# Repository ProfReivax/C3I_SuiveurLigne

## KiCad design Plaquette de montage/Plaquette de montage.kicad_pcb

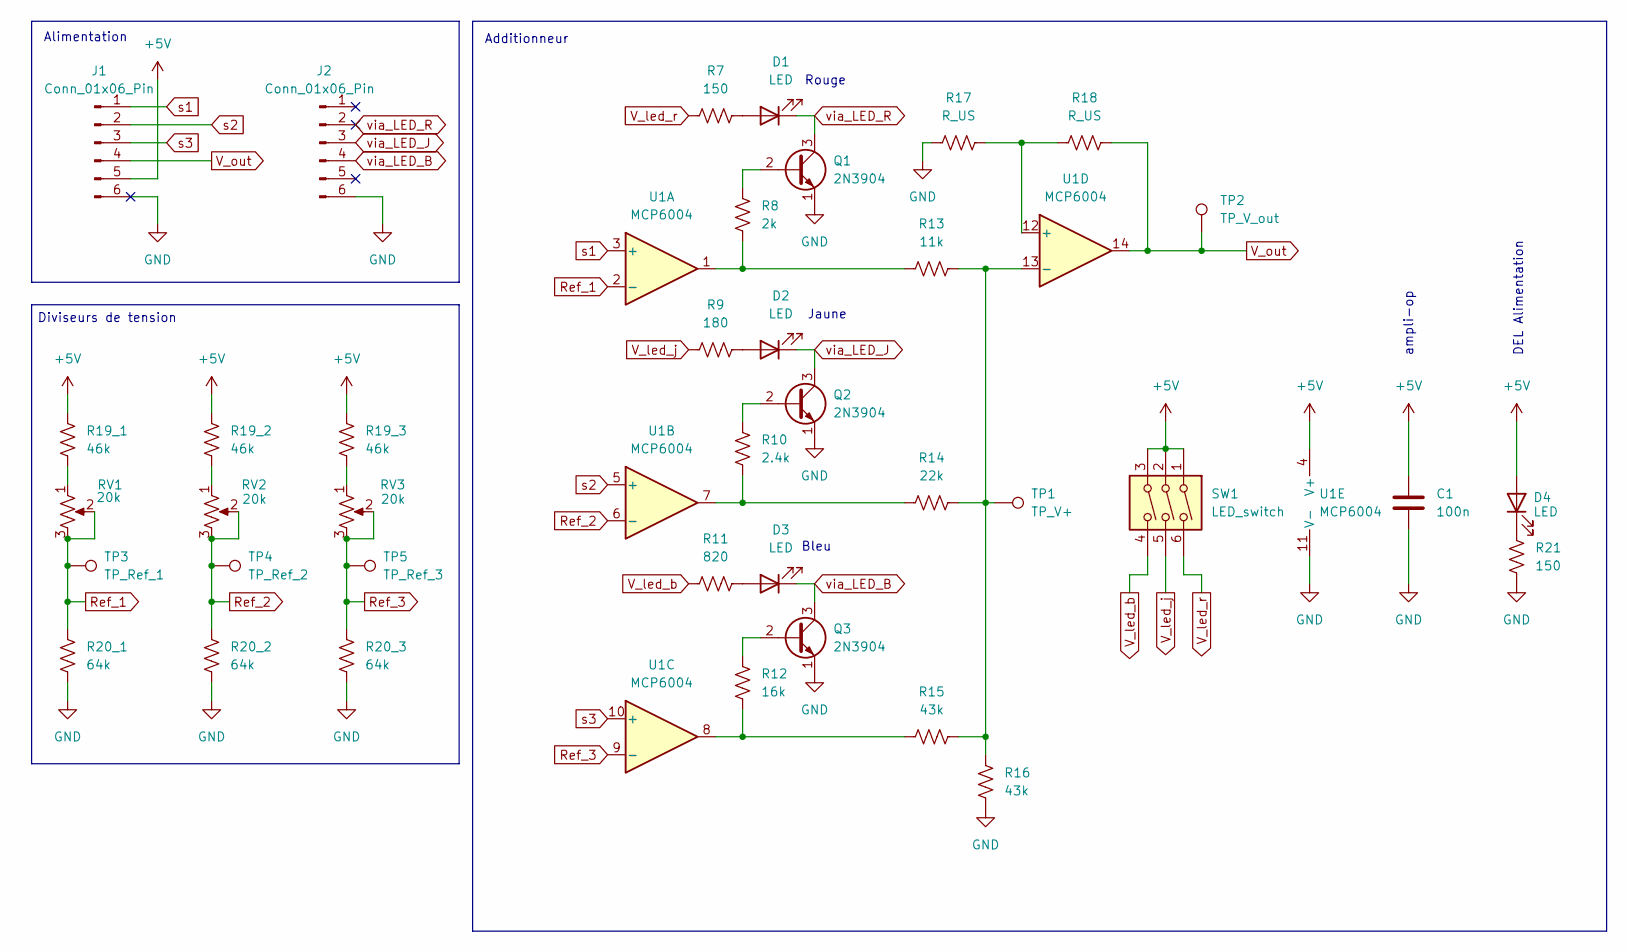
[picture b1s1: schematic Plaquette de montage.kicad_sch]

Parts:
C1: 100n; C_Disc_D3.0mm_W2.0mm_P2.50mm
D1, D2, D3, D4: LED; LED_D5.0mm
J1, J2: Conn_01x06_Pin; PinHeader_1x06_P2.54mm_Vertical
Q1, Q2, Q3: 2N3904; TO-92_Inline
R7, R21: 150; R_Axial_DIN0207_L6.3mm_D2.5mm_P10.16mm_Horizontal
R8: 2k; R_Axial_DIN0207_L6.3mm_D2.5mm_P10.16mm_Horizontal
R9: 180; R_Axial_DIN0207_L6.3mm_D2.5mm_P10.16mm_Horizontal
R10: 2.4k; R_Axial_DIN0207_L6.3mm_D2.5mm_P10.16mm_Horizontal
R11: 820; R_Axial_DIN0207_L6.3mm_D2.5mm_P10.16mm_Horizontal
R12: 16k; R_Axial_DIN0207_L6.3mm_D2.5mm_P10.16mm_Horizontal
R13: 11k; R_Axial_DIN0207_L6.3mm_D2.5mm_P10.16mm_Horizontal
R14: 22k; R_Axial_DIN0207_L6.3mm_D2.5mm_P10.16mm_Horizontal
R15, R16: 43k; R_Axial_DIN0207_L6.3mm_D2.5mm_P10.16mm_Horizontal
R17, R18: R_US; R_Axial_DIN0207_L6.3mm_D2.5mm_P10.16mm_Horizontal
R19_1, R19_2, R19_3: 46k; R_Axial_DIN0207_L6.3mm_D2.5mm_P10.16mm_Horizontal
R20_1, R20_2, R20_3: 64k; R_Axial_DIN0207_L6.3mm_D2.5mm_P10.16mm_Horizontal
RV1, RV2, RV3: 20k; Potentiometer_Bourns_3296W_Vertical
SW1: LED_switch; SW_DIP_SPSTx03_Slide_9.78x9.8mm_W7.62mm_P2.54mm
TP1: TP_V+; TestPoint_Loop_D2.50mm_Drill1.0mm
TP2: TP_V_out; TestPoint_Loop_D2.50mm_Drill1.0mm
TP3: TP_Ref_1; TestPoint_Loop_D2.50mm_Drill1.0mm
TP4: TP_Ref_2; TestPoint_Loop_D2.50mm_Drill1.0mm
TP5: TP_Ref_3; TestPoint_Loop_D2.50mm_Drill1.0mm
U1: MCP6004; CERDIP-14_W7.62mm_SideBrazed_LongPads_Socket

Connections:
+5V: C1.1, D4.2 (A), J1.5, R19_1.1, R19_2.1, R19_3.1, SW1.1, SW1.2, SW1.3, U1.4 (V+)
GND: C1.2, J1.6, J2.6, Q1.1 (E), Q2.1 (E), Q3.1 (E), R16.1, R17.1, R20_1.2, R20_2.2, R20_3.2, R21.2, U1.11 (V-)
unnamed: D1.2 (A), R7.2
unnamed: D2.2 (A), R9.2
unnamed: D3.2 (A), R11.2
unnamed: D4.1 (K), R21.1
unnamed: Q1.2 (B), R8.1
unnamed: Q2.2 (B), R10.1
unnamed: Q3.2 (B), R12.1
unnamed: R10.2, R14.1, U1.7
unnamed: R12.2, R15.1, U1.8
unnamed: R8.2, R13.1, U1.1
unnamed: R19_1.2, RV1.1
unnamed: R19_2.2, RV2.1
unnamed: R19_3.2, RV3.1
unnamed: R17.2, R18.1, U1.12 (+)
unnamed: R13.2, R14.2, R15.2, R16.2, TP1.1 (1_1), U1.13 (-)
Ref_1: R20_1.1, RV1.2, RV1.3, TP3.1 (1_1), U1.2 (-)
Ref_2: R20_2.1, RV2.2, RV2.3, TP4.1 (1_1), U1.6 (-)
Ref_3: R20_3.1, RV3.2, RV3.3, TP5.1 (1_1), U1.9 (-)
V_led_b: R11.1, SW1.4
V_led_j: R9.1, SW1.5
V_led_r: R7.1, SW1.6
V_out: J1.4, R18.2, TP2.1 (1_1), U1.14
s1: J1.1, U1.3 (+)
s2: J1.2, U1.5 (+)
s3: J1.3, U1.10 (+)
via_LED_B: D3.1 (K), J2.4, Q3.3 (C)
via_LED_J: D2.1 (K), J2.3, Q2.3 (C)
via_LED_R: D1.1 (K), J2.2, Q1.3 (C)

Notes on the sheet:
Bleu
Additionneur
Diviseurs de tension
Jaune
Alimentation
Rouge
ampli-op
DEL Alimentation

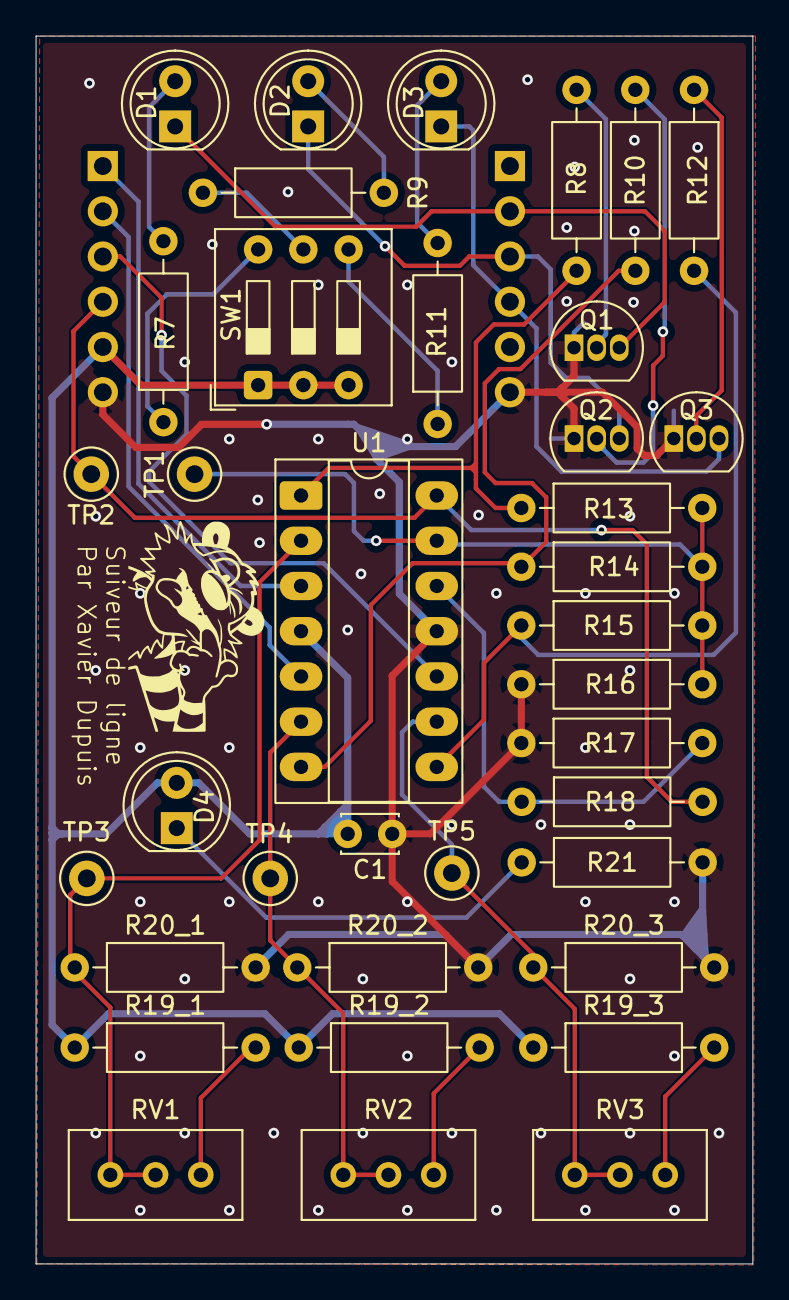
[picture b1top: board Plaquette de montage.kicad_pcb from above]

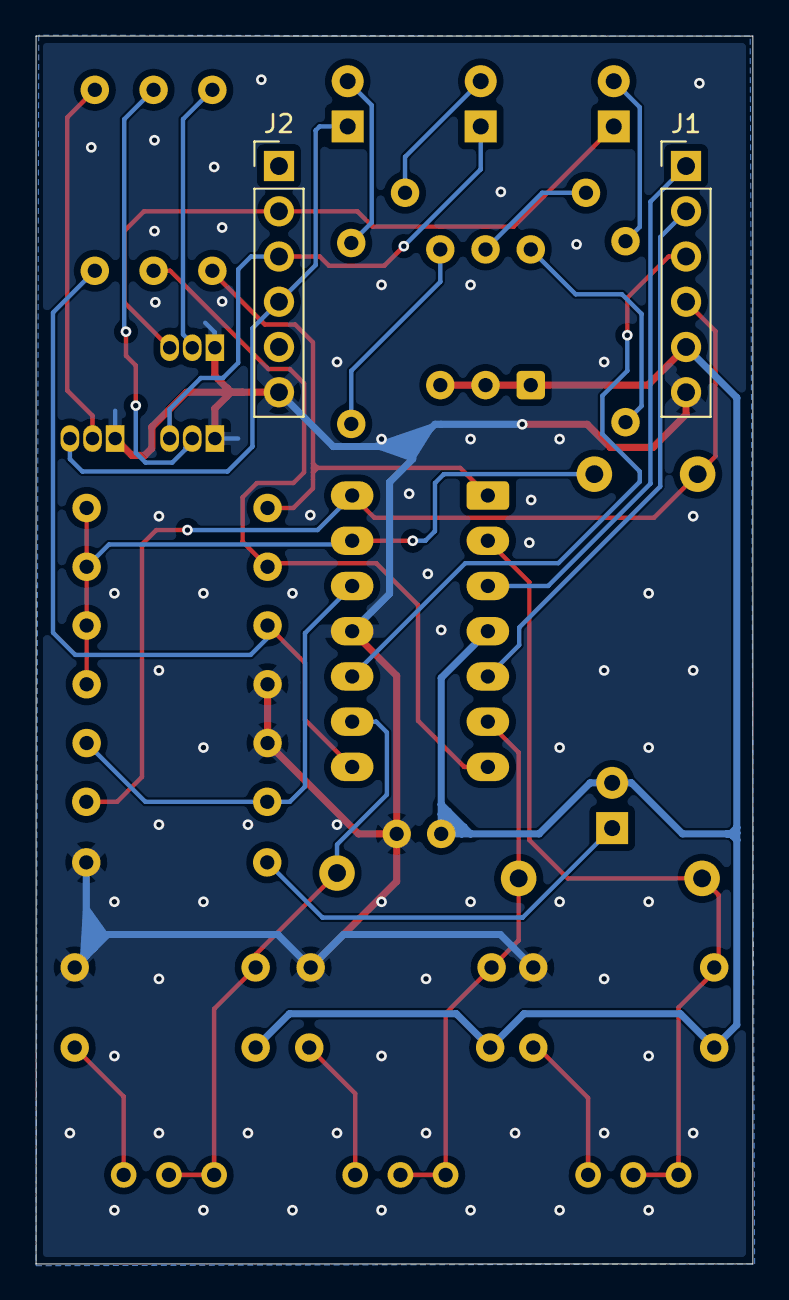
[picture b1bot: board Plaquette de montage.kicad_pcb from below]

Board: 2 copper layers, 40.2 x 69.0 mm, 39 parts (2 on the bottom side), 30 nets.
